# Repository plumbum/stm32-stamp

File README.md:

STM32 stamp boards collections
==============================

STM32 stamp board USB/SD/RS485/LCD
----------------------------------

    This board is now not fully tested!

Currently schematic placed at pcb/stm32-2inch40-usb-sd-proto.sch
and board placed at pcb/stm32-2inch40-usb-sd-proto.brd

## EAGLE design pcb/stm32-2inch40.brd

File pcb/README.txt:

STM32 boards
============

  * stm32-40.sch - модуль с экраном

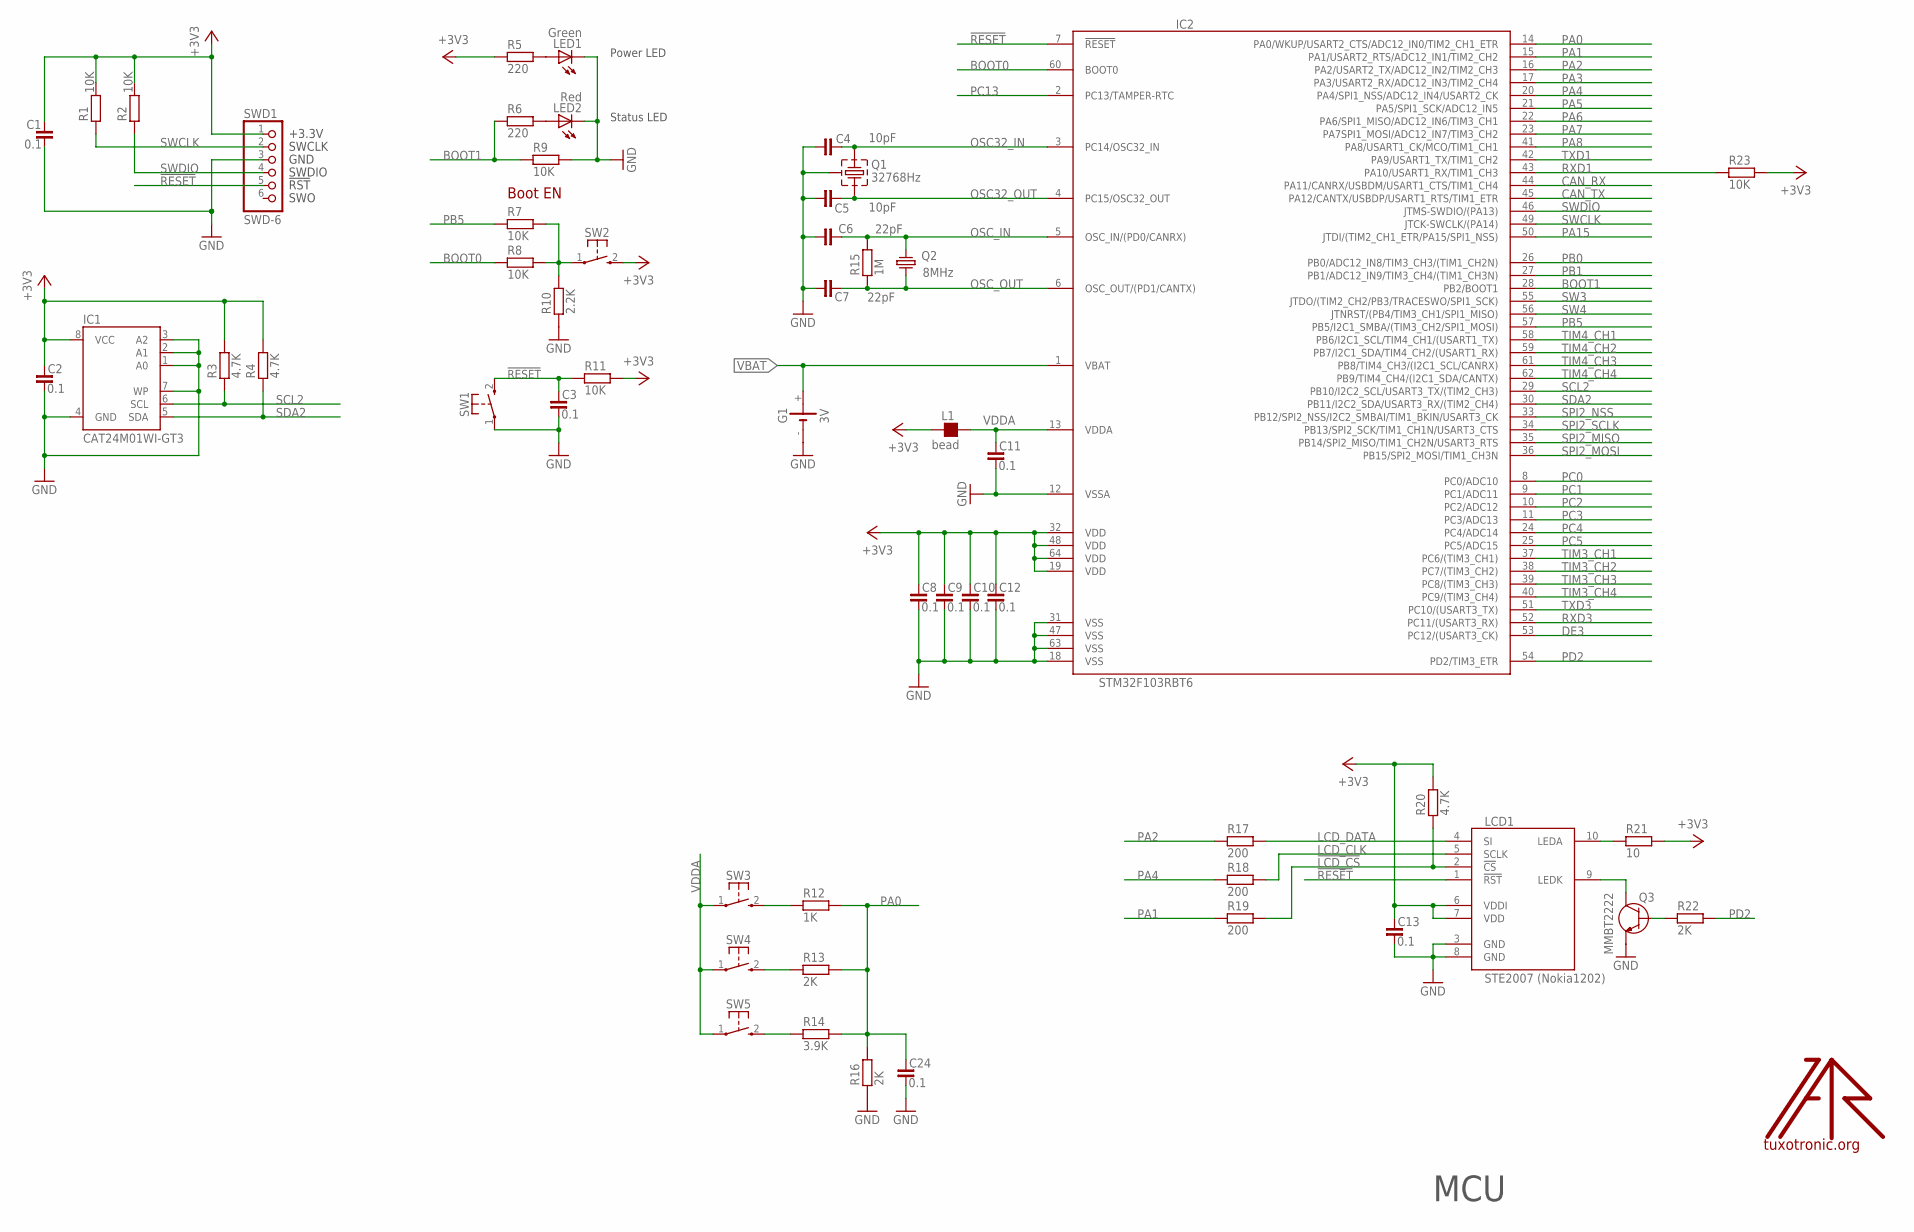
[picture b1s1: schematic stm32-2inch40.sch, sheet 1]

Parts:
C1, C2, C3, C8, C9, C10, C11, C12, C13, C24: 0.1; C0603
C4, C5: 10pF; C0603
C6, C7: 22pF; C0603
G1: 3V; SMT1220
IC1: CAT24M01WI-GT3; SO08
IC2: STM32F103RBT6; TQFP64
L1: bead; L0603
LCD1: STE2007 (Nokia1202); NOKIA1202LCD-EXT
LED1: Green; CHIP-LED0805
LED2: Red; CHIP-LED0805
Q1: 32768Hz; TC38H-G
Q2: 8MHz; HC49/S
Q3: MMBT2222; SOT23
R1, R2, R7, R8, R9, R11, R23: 10K; R0603
R3, R4, R20: 4.7K; R0603
R5, R6: 220; R0603
R10: 2.2K; R0603
R12: 1K; R0603
R13, R16, R22: 2K; R0603
R14: 3.9K; R0603
R15: 1M; R0603
R17, R18, R19: 200; R0603
R21: 10; R0603
SW1, SW2, SW3, SW4, SW5: KSS-2EG4430
SWD1: SWD-6; JTAG6PIN
U$1: LOGO; TT_LOGO

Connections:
!LCD_CS: LCD1.2 (!CS), R19.2, R20.1
!RESET: C3.1, IC2.7 (!RESET), LCD1.1 (!RST), R11.1, SW1.2 (S), SWD1.5
+3V3: C1.1, C2.1, C8.1, C9.1, C10.1, C12.1, C13.1, IC1.8 (VCC), IC2.19 (VDD), IC2.32 (VDD), IC2.48 (VDD), IC2.64 (VDD), L1.1, LCD1.6 (VDDI), LCD1.7 (VDD), R1.2, R2.2, R3.2, R4.2, R5.1, R11.2, R20.2, R21.2, R23.2, SW2.2 (S), SWD1.1; also elsewhere on the board
BOOT0: IC2.60 (BOOT0), R8.1
BOOT1: IC2.28 (PB2/BOOT1), R6.1, R9.1
CAN_RX: IC2.44 (PA11/CANRX/USBDM/USART1_CTS/TIM1_CH4); also elsewhere on the board
CAN_TX: IC2.45 (PA12/CANTX/USBDP/USART1_RTS/TIM1_ETR); also elsewhere on the board
DE3: IC2.53 (PC12/(USART3_CK)); also elsewhere on the board
GND: C1.2, C2.2, C3.2, C4.2, C5.2, C6.2, C7.2, C8.2, C9.2, C10.2, C11.2, C12.2, C13.2, C24.2, G1.-, IC1.1 (A0), IC1.2 (A1), IC1.3 (A2), IC1.4 (GND), IC1.7 (WP), IC2.12 (VSSA), IC2.18 (VSS), IC2.31 (VSS), IC2.47 (VSS), IC2.63 (VSS), LCD1.3 (GND), LCD1.8 (GND), LED1.C, LED2.C, Q1.GND, Q3.2 (E), R9.2, R10.1, R16.1, SW1.1, SWD1.3; also elsewhere on the board
LCD_CLK: LCD1.5 (SCLK), R18.2
LCD_DATA: LCD1.4 (SI), R17.2
unnamed: R7.2, R8.2, R10.2, SW2.1
unnamed: LED1.A, R5.2
unnamed: LCD1.9 (LEDK), Q3.3 (C)
unnamed: LED2.A, R6.2
unnamed: LCD1.10 (LEDA), R21.1
unnamed: Q3.1 (B), R22.1
unnamed: R12.1, SW3.2 (S)
unnamed: R13.1, SW4.2 (S)
unnamed: R14.1, SW5.2 (S)
OSC32_IN: C4.1, IC2.3 (PC14/OSC32_IN), Q1.2
OSC32_OUT: C5.1, IC2.4 (PC15/OSC32_OUT), Q1.1
OSC_IN: C6.1, IC2.5 (OSC_IN/(PD0/CANRX)), Q2.1, R15.2
OSC_OUT: C7.1, IC2.6 (OSC_OUT/(PD1/CANTX)), Q2.2, R15.1
PA0: C24.1, IC2.14 (PA0/WKUP/USART2_CTS/ADC12_IN0/TIM2_CH1_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), R12.2, R13.2, R14.2, R16.2; also elsewhere on the board
PA1: IC2.15 (PA1/USART2_RTS/ADC12_IN1/TIM2_CH2), R19.1; also elsewhere on the board
PA2: IC2.16 (PA2/USART2_TX/ADC12_IN2/TIM2_CH3), R17.1; also elsewhere on the board
PA3: IC2.17 (PA3/USART2_RX/ADC12_IN3/TIM2_CH4); also elsewhere on the board
PA4: IC2.20 (PA4/SPI1_NSS/ADC12_IN4/USART2_CK), R18.1; also elsewhere on the board
PA5: IC2.21 (PA5/SPI1_SCK/ADC12_IN5); also elsewhere on the board
PA6: IC2.22 (PA6/SPI1_MISO/ADC12_IN6/TIM3_CH1); also elsewhere on the board
PA7: IC2.23 (PA7SPI1_MOSI/ADC12_IN7/TIM3_CH2); also elsewhere on the board
PA8: IC2.41 (PA8/USART1_CK/MCO/TIM1_CH1); also elsewhere on the board
PA15: IC2.50 (JTDI/(TIM2_CH1_ETR/PA15/SPI1_NSS)); also elsewhere on the board
PB0: IC2.26 (PB0/ADC12_IN8/TIM3_CH3/(TIM1_CH2N)); also elsewhere on the board
PB1: IC2.27 (PB1/ADC12_IN9/TIM3_CH4/(TIM1_CH3N)); also elsewhere on the board
PB5: IC2.57 (PB5/I2C1_SMBA/(TIM3_CH2/SPI1_MOSI)), R7.1
PC0: IC2.8 (PC0/ADC10); also elsewhere on the board
PC1: IC2.9 (PC1/ADC11); also elsewhere on the board
PC2: IC2.10 (PC2/ADC12); also elsewhere on the board
PC3: IC2.11 (PC3/ADC13); also elsewhere on the board
PC4: IC2.24 (PC4/ADC14); also elsewhere on the board
PC5: IC2.25 (PC5/ADC15); also elsewhere on the board
PC13: IC2.2 (PC13/TAMPER-RTC); also elsewhere on the board
PD2: IC2.54 (PD2/TIM3_ETR), R22.2; also elsewhere on the board
RXD1: IC2.43 (PA10/USART1_RX/TIM1_CH3), R23.1; also elsewhere on the board
RXD3: IC2.52 (PC11/(USART3_RX)); also elsewhere on the board
SCL2: IC1.6 (SCL), IC2.29 (PB10/I2C2_SCL/USART3_TX/(TIM2_CH3)), R3.1; also elsewhere on the board
SDA2: IC1.5 (SDA), IC2.30 (PB11/I2C2_SDA/USART3_RX/(TIM2_CH4)), R4.1; also elsewhere on the board
SPI2_MISO: IC2.35 (PB14/SPI2_MISO/TIM1_CH2N/USART3_RTS); also elsewhere on the board
SPI2_MOSI: IC2.36 (PB15/SPI2_MOSI/TIM1_CH3N); also elsewhere on the board
SPI2_NSS: IC2.33 (PB12/SPI2_NSS/I2C2_SMBAI/TIM1_BKIN/USAR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); also elsewhere on the board
SPI2_SCLK: IC2.34 (PB13/SPI2_SCK/TIM1_CH1N/USART3_CTS); also elsewhere on the board
SW3: IC2.55 (JTDO/(TIM2_CH2/PB3/TRACESWO/SPI1_SCK)); also elsewhere on the board
SW4: IC2.56 (JTNRST/(PB4/TIM3_CH1/SPI1_MISO)); also elsewhere on the board
SWCLK: IC2.49 (JTCK-SWCLK/(PA14)), R1.1, SWD1.2
SWDIO: IC2.46 (JTMS-SWDIO/(PA13)), R2.1, SWD1.4
TIM3_CH1: IC2.37 (PC6/(TIM3_CH1)); also elsewhere on the board
TIM3_CH2: IC2.38 (PC7/(TIM3_CH2)); also elsewhere on the board
TIM3_CH3: IC2.39 (PC8/(TIM3_CH3)); also elsewhere on the board
TIM3_CH4: IC2.40 (PC9/(TIM3_CH4)); also elsewhere on the board
TIM4_CH1: IC2.58 (PB6/I2C1_SCL/TIM4_CH1/(USART1_TX)); also elsewhere on the board
TIM4_CH2: IC2.59 (PB7/I2C1_SDA/TIM4_CH2/(USART1_RX)); also elsewhere on the board
TIM4_CH3: IC2.61 (PB8/TIM4_CH3/(I2C1_SCL/CANRX)); also elsewhere on the board
TIM4_CH4: IC2.62 (PB9/TIM4_CH4/(I2C1_SDA/CANTX)); also elsewhere on the board
TXD1: IC2.42 (PA9/USART1_TX/TIM1_CH2); also elsewhere on the board
TXD3: IC2.51 (PC10/(USART3_TX)); also elsewhere on the board
VBAT: G1.+, IC2.1 (VBAT)
VDDA: C11.1, IC2.13 (VDDA), L1.2, SW3.1, SW4.1, SW5.1

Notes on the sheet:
Boot EN
Status LED
MCU
Power LED

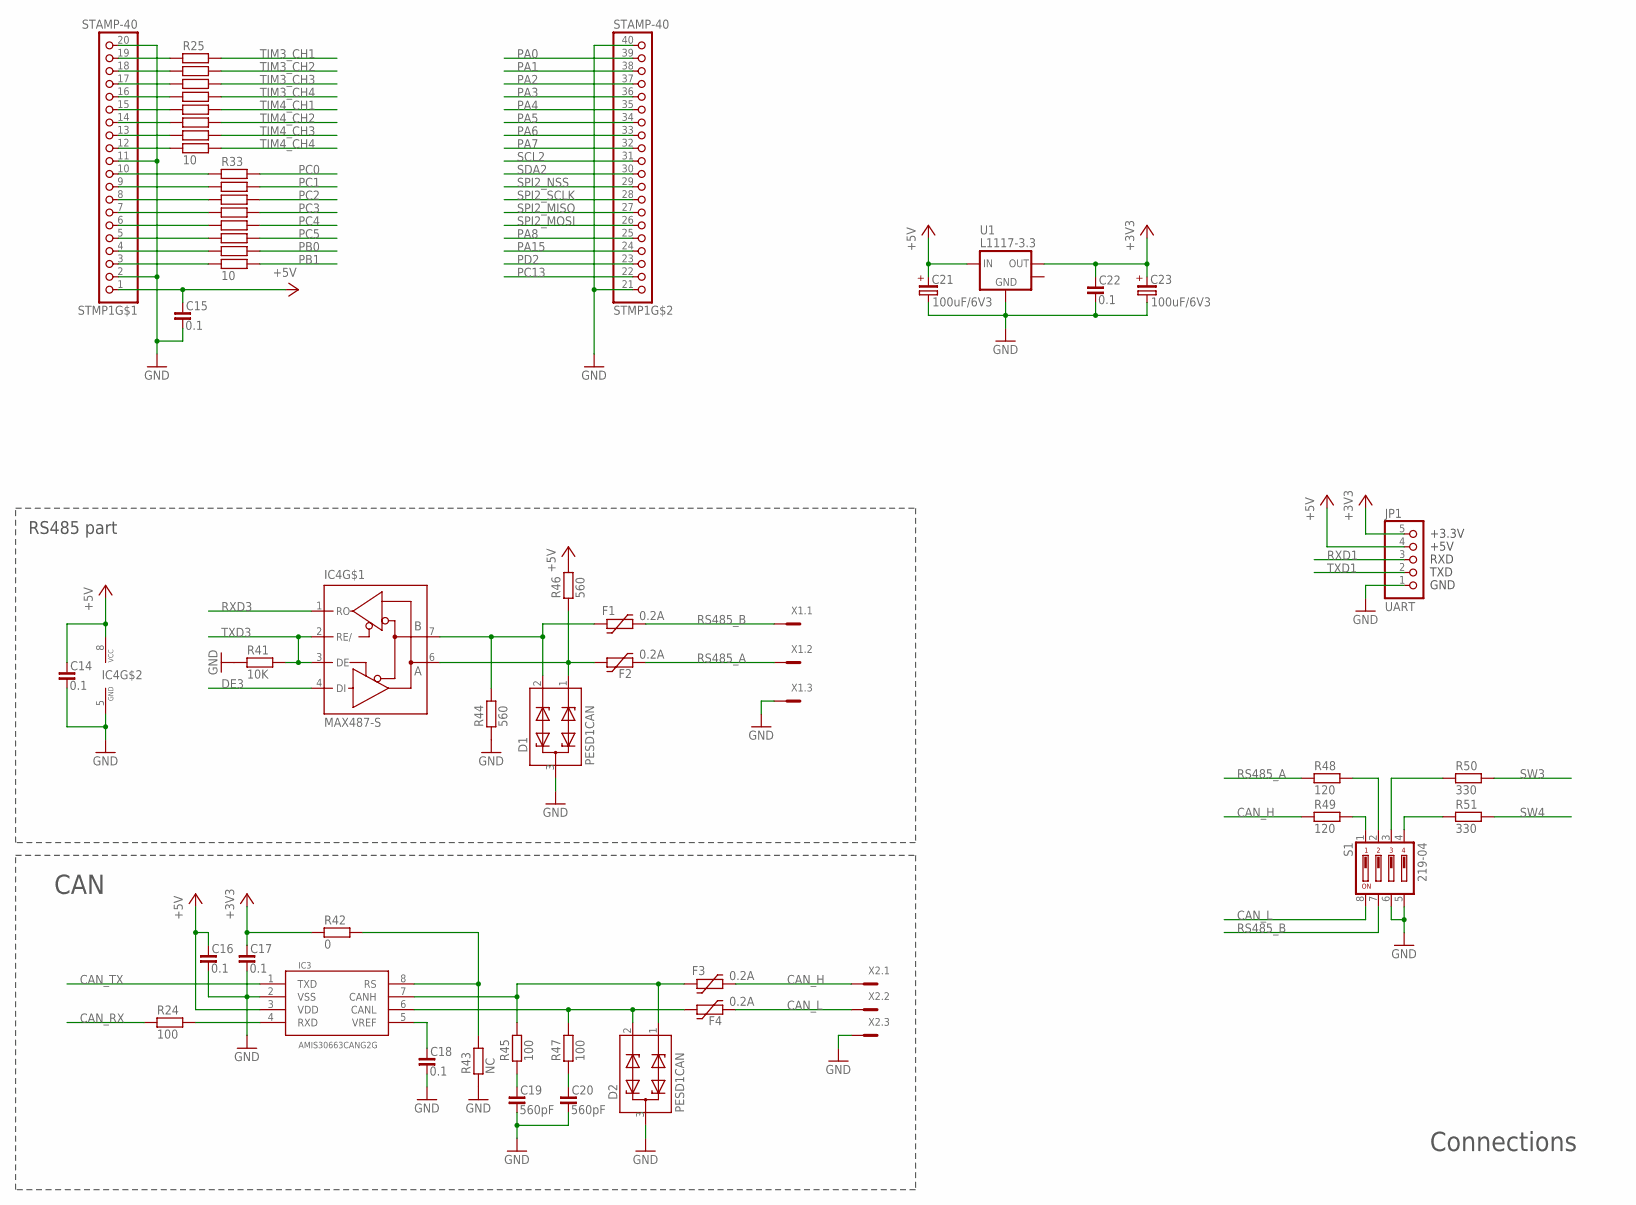
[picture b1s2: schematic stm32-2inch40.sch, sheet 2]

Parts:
C14, C16, C17, C18: 0.1; C0603
C15, C22: 0.1; C0805
C19, C20: 560pF; C0603
C21, C23: 100uF/6V3; SMC_D
D1, D2: PESD1CAN; SOT23
F1, F2, F3, F4: 0.2A; 1206L
IC3: AMIS30663CANG2G; SO08
IC4: MAX487-S; SO08
JP1: UART; UART_1X05
R24, R45, R47: 100; R0603
R25, R26, R27, R28, R29, R30, R31, R32, R33, R34, R35, R36, R37, R38, R39, R40: 10; R0603
R41: 10K; R0603
R42: 0; R0603
R43: NC; R0603
R44, R46: 560; R0603
R48, R49: 120; R0805
R50, R51: 330; R0603
S1: 219-04; CTS-219-04
STMP1: STAMP-40
U1: L1117-3.3; SOT223
X1, X2: MCV3

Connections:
+3V3: C17.1, C22.1, C23.+, JP1.5, R42.1, U1.2 (OUT); also elsewhere on the board
+5V: C14.1, C15.1, C16.1, C21.+, IC3.3 (VDD), IC4.8 (VCC), JP1.4, R46.2, STMP1.1, U1.3 (IN)
CAN_CTRL: IC3.8 (RS), R42.2, R43.2
CAN_H: F3.P$2 (2), R49.1, X2.1
CAN_L: F4.P$2 (2), S1.8, X2.2
CAN_RX: R24.1; also elsewhere on the board
CAN_TX: IC3.1 (TXD); also elsewhere on the board
DE3: IC4.4 (DI); also elsewhere on the board
GND: C14.2, C15.2, C16.2, C17.2, C18.2, C19.2, C20.2, C21.-, C22.2, C23.-, D1.3, D2.3, IC3.2 (VSS), IC4.5 (GND), JP1.1, R41.1, R43.1, R44.1, S1.5, S1.6, STMP1.2, STMP1.11, STMP1.20, STMP1.21 (1), STMP1.40 (20), U1.1 (GND), X1.3, X2.3; also elsewhere on the board
unnamed: C18.1, IC3.5 (VREF)
unnamed: R49.2, S1.1
unnamed: D1.2, F1.P$1 (1), IC4.7 (B), R44.2
unnamed: IC3.4 (RXD), R24.2
unnamed: R48.2, S1.2
unnamed: R50.1, S1.3
unnamed: R51.1, S1.4
unnamed: R33.1, STMP1.10
unnamed: R34.1, STMP1.9
unnamed: R25.1, STMP1.19
unnamed: R26.1, STMP1.18
unnamed: R27.1, STMP1.17
unnamed: R28.1, STMP1.16
unnamed: R29.1, STMP1.15
unnamed: R30.1, STMP1.14
unnamed: R31.1, STMP1.13
unnamed: R32.1, STMP1.12
unnamed: R35.1, STMP1.8
unnamed: R36.1, STMP1.7
unnamed: R37.1, STMP1.6
unnamed: R38.1, STMP1.5
unnamed: R39.1, STMP1.4
unnamed: R40.1, STMP1.3
unnamed: D1.1, F2.P$1 (1), IC4.6 (A), R46.1
unnamed: D2.1, F3.P$1 (1), IC3.7 (CANH), R45.2
unnamed: D2.2, F4.P$1 (1), IC3.6 (CANL), R47.2
unnamed: C20.1, R47.1
unnamed: C19.1, R45.1
PA0: STMP1.39 (19); also elsewhere on the board
PA1: STMP1.38 (18); also elsewhere on the board
PA2: STMP1.37 (17); also elsewhere on the board
PA3: STMP1.36 (16); also elsewhere on the board
PA4: STMP1.35 (15); also elsewhere on the board
PA5: STMP1.34 (14); also elsewhere on the board
PA6: STMP1.33 (13); also elsewhere on the board
PA7: STMP1.32 (12); also elsewhere on the board
PA8: STMP1.25 (5); also elsewhere on the board
PA15: STMP1.24 (4); also elsewhere on the board
PB0: R39.2; also elsewhere on the board
PB1: R40.2; also elsewhere on the board
PC0: R33.2; also elsewhere on the board
PC1: R34.2; also elsewhere on the board
PC2: R35.2; also elsewhere on the board
PC3: R36.2; also elsewhere on the board
PC4: R37.2; also elsewhere on the board
PC5: R38.2; also elsewhere on the board
PC13: STMP1.22 (2); also elsewhere on the board
PD2: STMP1.23 (3); also elsewhere on the board
RS485_A: F2.P$2 (2), R48.1, X1.2
RS485_B: F1.P$2 (2), S1.7, X1.1
RXD1: JP1.3; also elsewhere on the board
RXD3: IC4.1 (RO); also elsewhere on the board
SCL2: STMP1.31 (11); also elsewhere on the board
SDA2: STMP1.30 (10); also elsewhere on the board
SPI2_MISO: STMP1.27 (7); also elsewhere on the board
SPI2_MOSI: STMP1.26 (6); also elsewhere on the board
SPI2_NSS: STMP1.29 (9); also elsewhere on the board
SPI2_SCLK: STMP1.28 (8); also elsewhere on the board
SW3: R50.2; also elsewhere on the board
SW4: R51.2; also elsewhere on the board
TIM3_CH1: R25.2; also elsewhere on the board
TIM3_CH2: R26.2; also elsewhere on the board
TIM3_CH3: R27.2; also elsewhere on the board
TIM3_CH4: R28.2; also elsewhere on the board
TIM4_CH1: R29.2; also elsewhere on the board
TIM4_CH2: R30.2; also elsewhere on the board
TIM4_CH3: R31.2; also elsewhere on the board
TIM4_CH4: R32.2; also elsewhere on the board
TXD1: JP1.2; also elsewhere on the board
TXD3: IC4.2 (RE/), IC4.3 (DE), R41.2; also elsewhere on the board

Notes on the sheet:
Connections
CAN
RS485 part

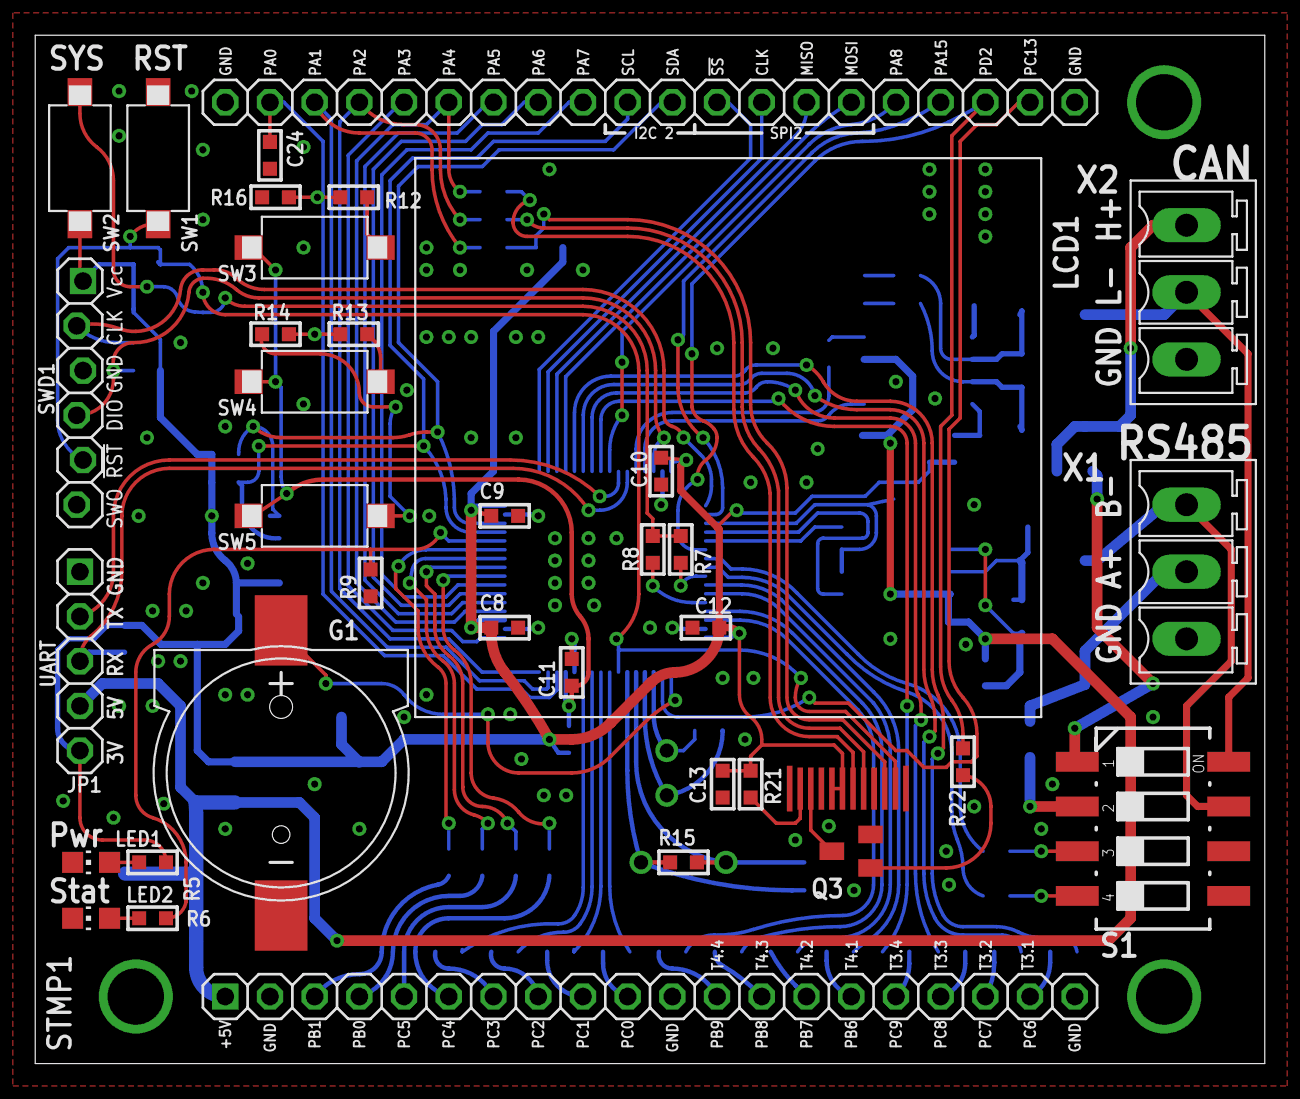
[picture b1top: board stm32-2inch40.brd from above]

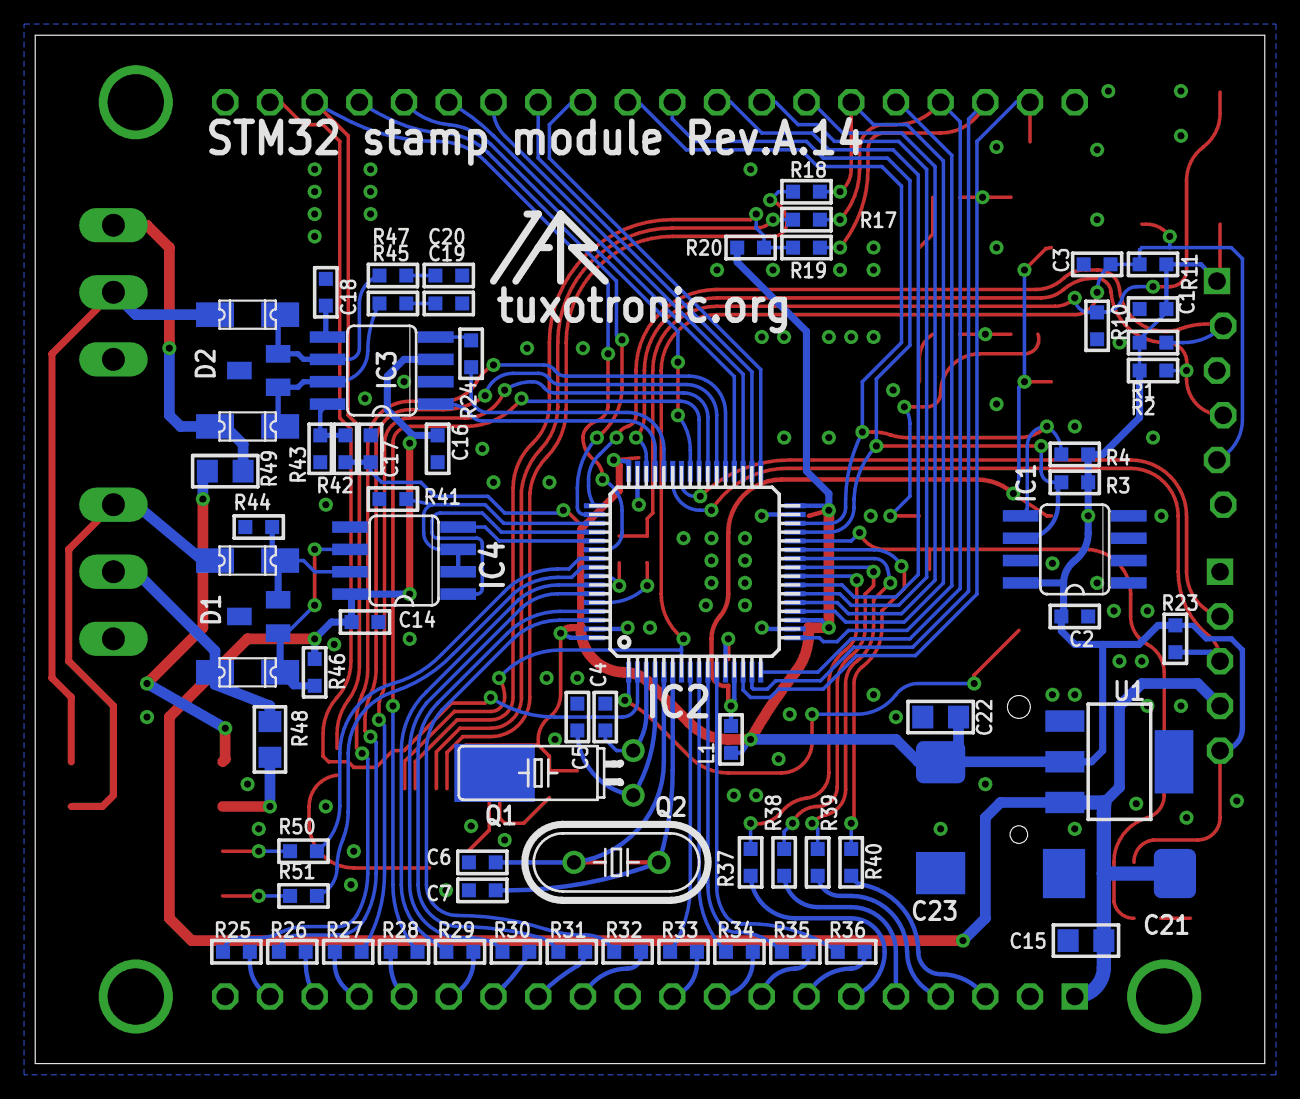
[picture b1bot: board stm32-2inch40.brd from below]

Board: 2 copper layers, 69.8 x 58.4 mm, 106 parts (71 on the bottom side), 103 nets.

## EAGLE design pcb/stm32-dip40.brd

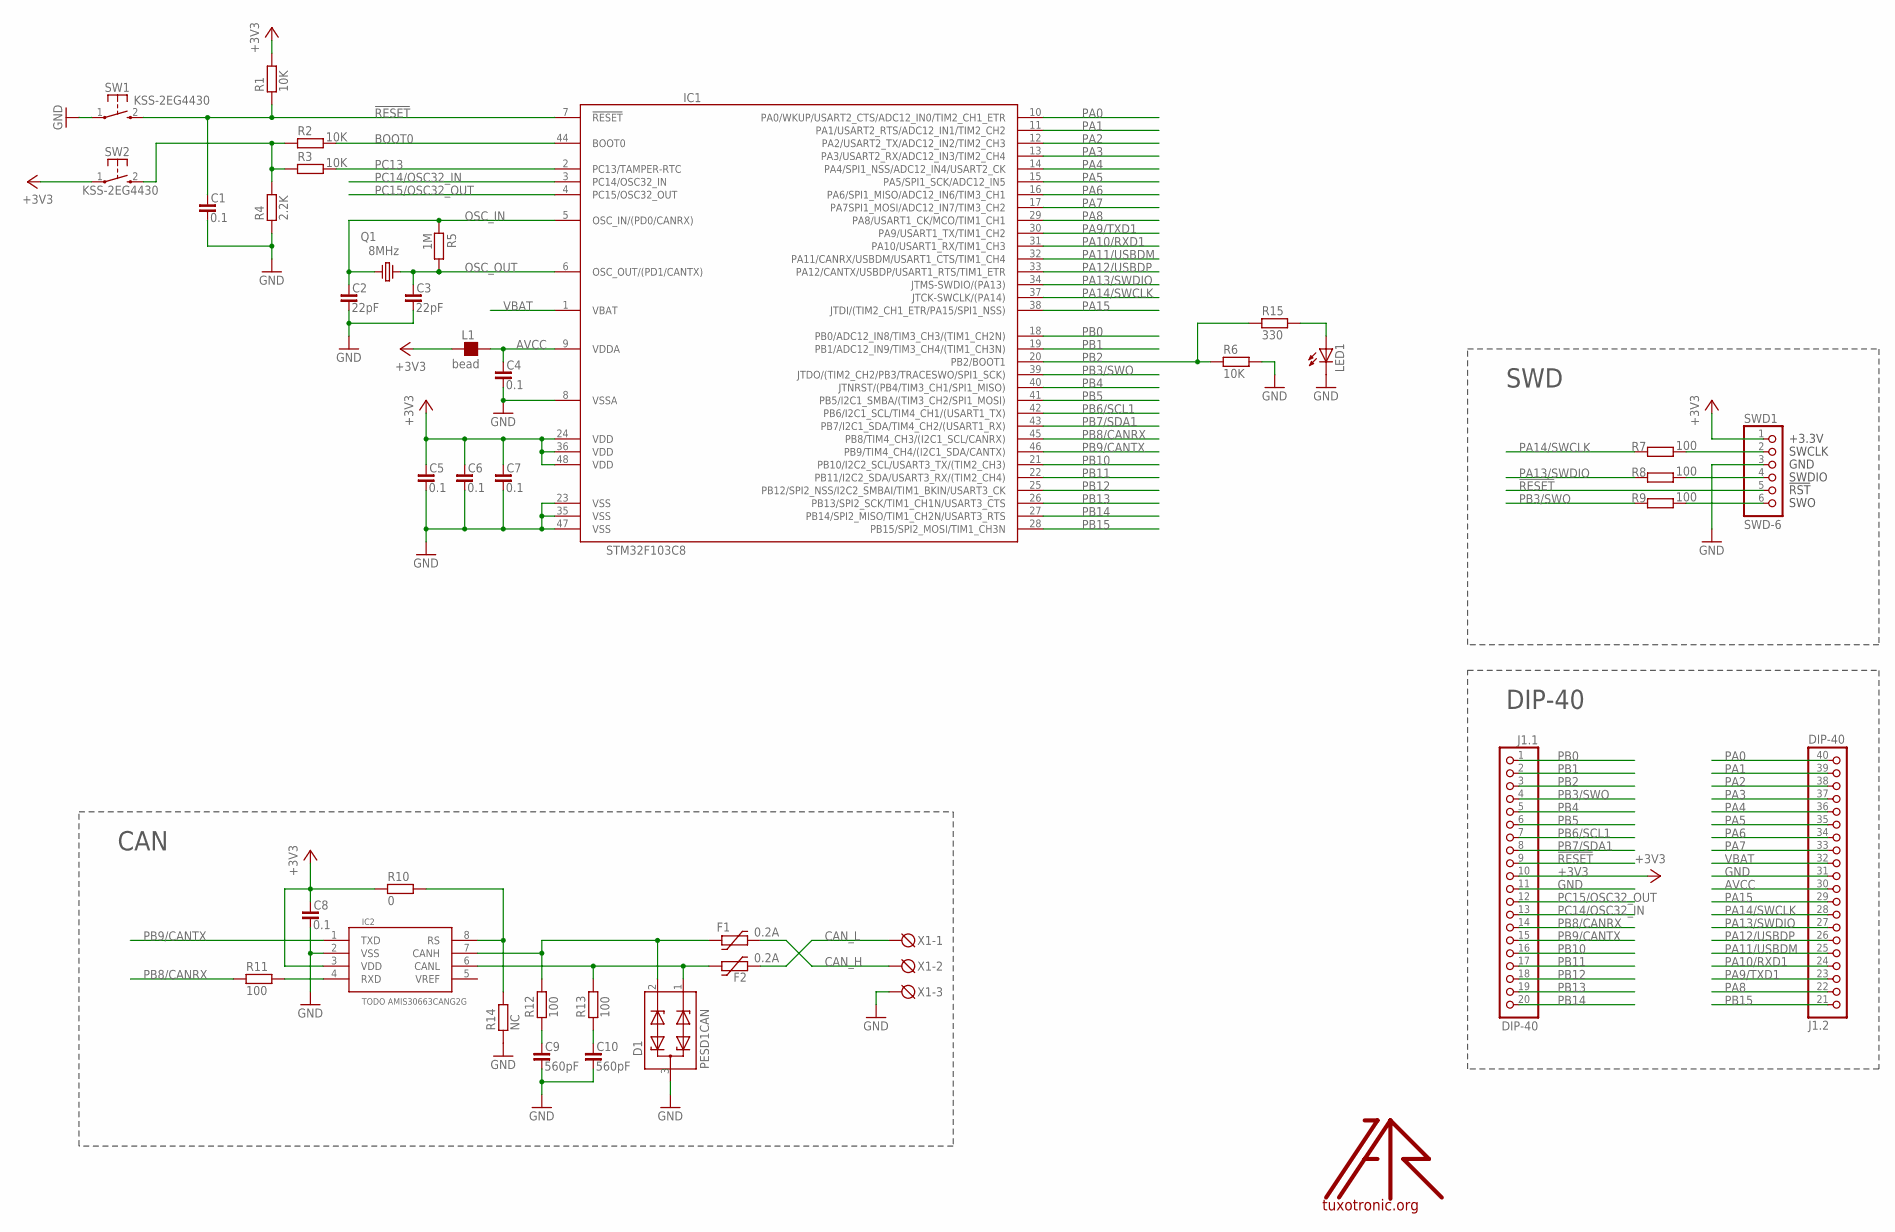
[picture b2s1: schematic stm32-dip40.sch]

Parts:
C1, C4, C5, C6, C7, C8: 0.1; C0603
C2, C3: 22pF; C0603
C9, C10: 560pF; C0603
D1: PESD1CAN; SOT23
F1, F2: 0.2A; 1206L
IC1: STM32F103C8; LQFP48
IC2: TODO AMIS30663CANG2G; SO08
J1: DIP-40
L1: bead; L0603
LED1: LEDCHIPLED_0603; CHIPLED_0603
Q1: 8MHz; HC49/S
R1, R2, R3, R6: 10K; R0603
R4: 2.2K; R0603
R5: 1M; R0603
R7, R8, R9, R11, R12, R13: 100; R0603
R10: 0; R0603
R14: NC; R0603
R15: 330; R0603
SW1, SW2: KSS-2EG4430
SWD1: SWD-6; JTAG6PIN
U$: LOGO; TT_LOGO
X1: DG3XX-03-3.5; DG350-3.5-03P

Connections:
!RESET: C1.1, IC1.7 (!RESET), J1.9, R1.1, SW1.2 (S), SWD1.5
+3V3: C5.1, C6.1, C7.1, C8.1, IC1.24 (VDD), IC1.36 (VDD), IC1.48 (VDD), IC2.3 (VDD), J1.10, L1.1, R1.2, R10.1, SW2.1, SWD1.1
AVCC: C4.1, IC1.9 (VDDA), J1.30 (10), L1.2
BOOT0: IC1.44 (BOOT0), R2.2
CAN_CTRL: IC2.8 (RS), R10.2, R14.2
CAN_H: F1.P$2 (2), X1.2
CAN_L: F2.P$2 (2), X1.1
GND: C1.2, C2.2, C3.2, C4.2, C5.2, C6.2, C7.2, C8.2, C9.2, C10.2, D1.3, IC1.8 (VSSA), IC1.23 (VSS), IC1.35 (VSS), IC1.47 (VSS), IC2.2 (VSS), J1.11, J1.31 (11), LED1.C, R4.1, R6.2, R14.1, SW1.1, SWD1.3, X1.3
unnamed: R2.1, R3.1, R4.2, SW2.2 (S)
unnamed: R7.2, SWD1.2
unnamed: R8.2, SWD1.4
unnamed: R9.2, SWD1.6
unnamed: LED1.A, R15.2
unnamed: IC2.4 (RXD), R11.2
unnamed: D1.2, F1.P$1 (1), IC2.7 (CANH), R12.2
unnamed: D1.1, F2.P$1 (1), IC2.6 (CANL), R13.2
unnamed: C10.1, R13.1
unnamed: C9.1, R12.1
OSC_IN: C2.1, IC1.5 (OSC_IN/(PD0/CANRX)), Q1.1, R5.1
OSC_OUT: C3.1, IC1.6 (OSC_OUT/(PD1/CANTX)), Q1.2, R5.2
PA0: IC1.10 (PA0/WKUP/USART2_CTS/ADC12_IN0/TIM2_CH1_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), J1.40 (20)
PA1: IC1.11 (PA1/USART2_RTS/ADC12_IN1/TIM2_CH2), J1.39 (19)
PA2: IC1.12 (PA2/USART2_TX/ADC12_IN2/TIM2_CH3), J1.38 (18)
PA3: IC1.13 (PA3/USART2_RX/ADC12_IN3/TIM2_CH4), J1.37 (17)
PA4: IC1.14 (PA4/SPI1_NSS/ADC12_IN4/USART2_CK), J1.36 (16)
PA5: IC1.15 (PA5/SPI1_SCK/ADC12_IN5), J1.35 (15)
PA6: IC1.16 (PA6/SPI1_MISO/ADC12_IN6/TIM3_CH1), J1.34 (14)
PA7: IC1.17 (PA7SPI1_MOSI/ADC12_IN7/TIM3_CH2), J1.33 (13)
PA8: IC1.29 (PA8/USART1_CK/MCO/TIM1_CH1), J1.22 (2)
PA9/TXD1: IC1.30 (PA9/USART1_TX/TIM1_CH2), J1.23 (3)
PA10/RXD1: IC1.31 (PA10/USART1_RX/TIM1_CH3), J1.24 (4)
PA11/USBDM: IC1.32 (PA11/CANRX/USBDM/USART1_CTS/TIM1_CH4), J1.25 (5)
PA12/USBDP: IC1.33 (PA12/CANTX/USBDP/USART1_RTS/TIM1_ETR), J1.26 (6)
PA13/SWDIO: IC1.34 (JTMS-SWDIO/(PA13)), J1.27 (7), R8.1
PA14/SWCLK: IC1.37 (JTCK-SWCLK/(PA14)), J1.28 (8), R7.1
PA15: IC1.38 (JTDI/(TIM2_CH1_ETR/PA15/SPI1_NSS)), J1.29 (9)
PB0: IC1.18 (PB0/ADC12_IN8/TIM3_CH3/(TIM1_CH2N)), J1.1
PB1: IC1.19 (PB1/ADC12_IN9/TIM3_CH4/(TIM1_CH3N)), J1.2
PB2: IC1.20 (PB2/BOOT1), J1.3, R6.1, R15.1
PB3/SWO: IC1.39 (JTDO/(TIM2_CH2/PB3/TRACESWO/SPI1_SCK)), J1.4, R9.1
PB4: IC1.40 (JTNRST/(PB4/TIM3_CH1/SPI1_MISO)), J1.5
PB5: IC1.41 (PB5/I2C1_SMBA/(TIM3_CH2/SPI1_MOSI)), J1.6
PB6/SCL1: IC1.42 (PB6/I2C1_SCL/TIM4_CH1/(USART1_TX)), J1.7
PB7/SDA1: IC1.43 (PB7/I2C1_SDA/TIM4_CH2/(USART1_RX)), J1.8
PB8/CANRX: IC1.45 (PB8/TIM4_CH3/(I2C1_SCL/CANRX)), J1.14, R11.1
PB9/CANTX: IC1.46 (PB9/TIM4_CH4/(I2C1_SDA/CANTX)), IC2.1 (TXD), J1.15
PB10: IC1.21 (PB10/I2C2_SCL/USART3_TX/(TIM2_CH3)), J1.16
PB11: IC1.22 (PB11/I2C2_SDA/USART3_RX/(TIM2_CH4)), J1.17
PB12: IC1.25 (PB12/SPI2_NSS/I2C2_SMBAI/TIM1_BKIN/USAR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), J1.18
PB13: IC1.26 (PB13/SPI2_SCK/TIM1_CH1N/USART3_CTS), J1.19
PB14: IC1.27 (PB14/SPI2_MISO/TIM1_CH2N/USART3_RTS), J1.20
PB15: IC1.28 (PB15/SPI2_MOSI/TIM1_CH3N), J1.21 (1)
PC13: IC1.2 (PC13/TAMPER-RTC), R3.2
PC14/OSC32_IN: IC1.3 (PC14/OSC32_IN), J1.13
PC15/OSC32_OUT: IC1.4 (PC15/OSC32_OUT), J1.12
VBAT: IC1.1 (VBAT), J1.32 (12)

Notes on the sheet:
CAN
DIP-40
SWD

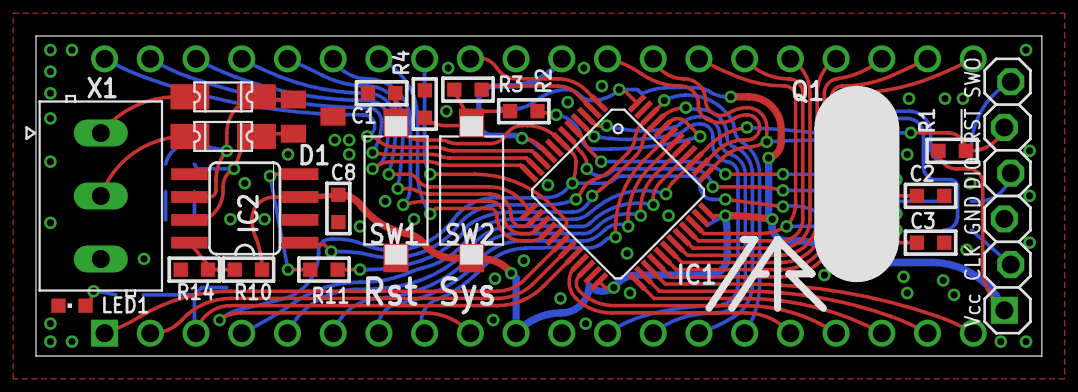
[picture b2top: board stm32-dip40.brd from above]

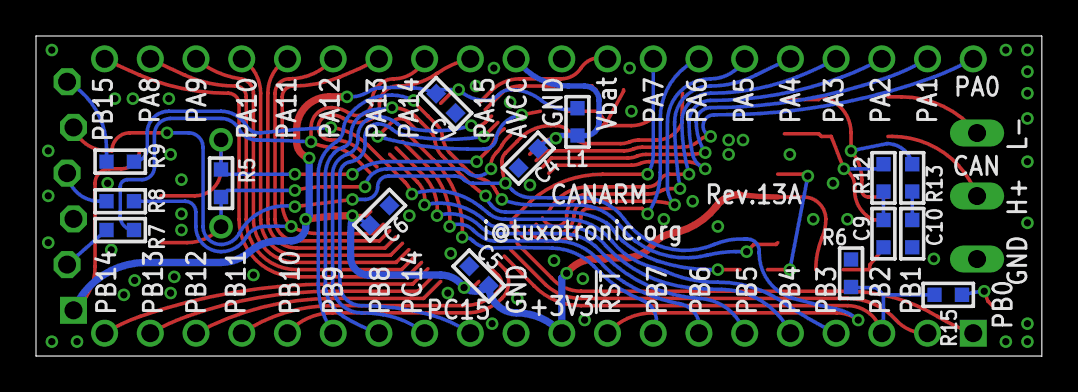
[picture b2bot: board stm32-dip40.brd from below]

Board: 2 copper layers, 55.9 x 17.8 mm, 39 parts (15 on the bottom side), 56 nets.

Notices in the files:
parts and their libraries:
vreg-linear: 2009 Draw by Ivan A-R. License CC-BY-SA 3.0
rc-master: Copyright (C) 2007, Bob Starr
